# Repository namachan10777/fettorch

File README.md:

# fettorch
bootstrap式モータードライバ

# TODO
 * 回路定数の決定
 * 電源供給基板の設計
# Licence
MIT Licence

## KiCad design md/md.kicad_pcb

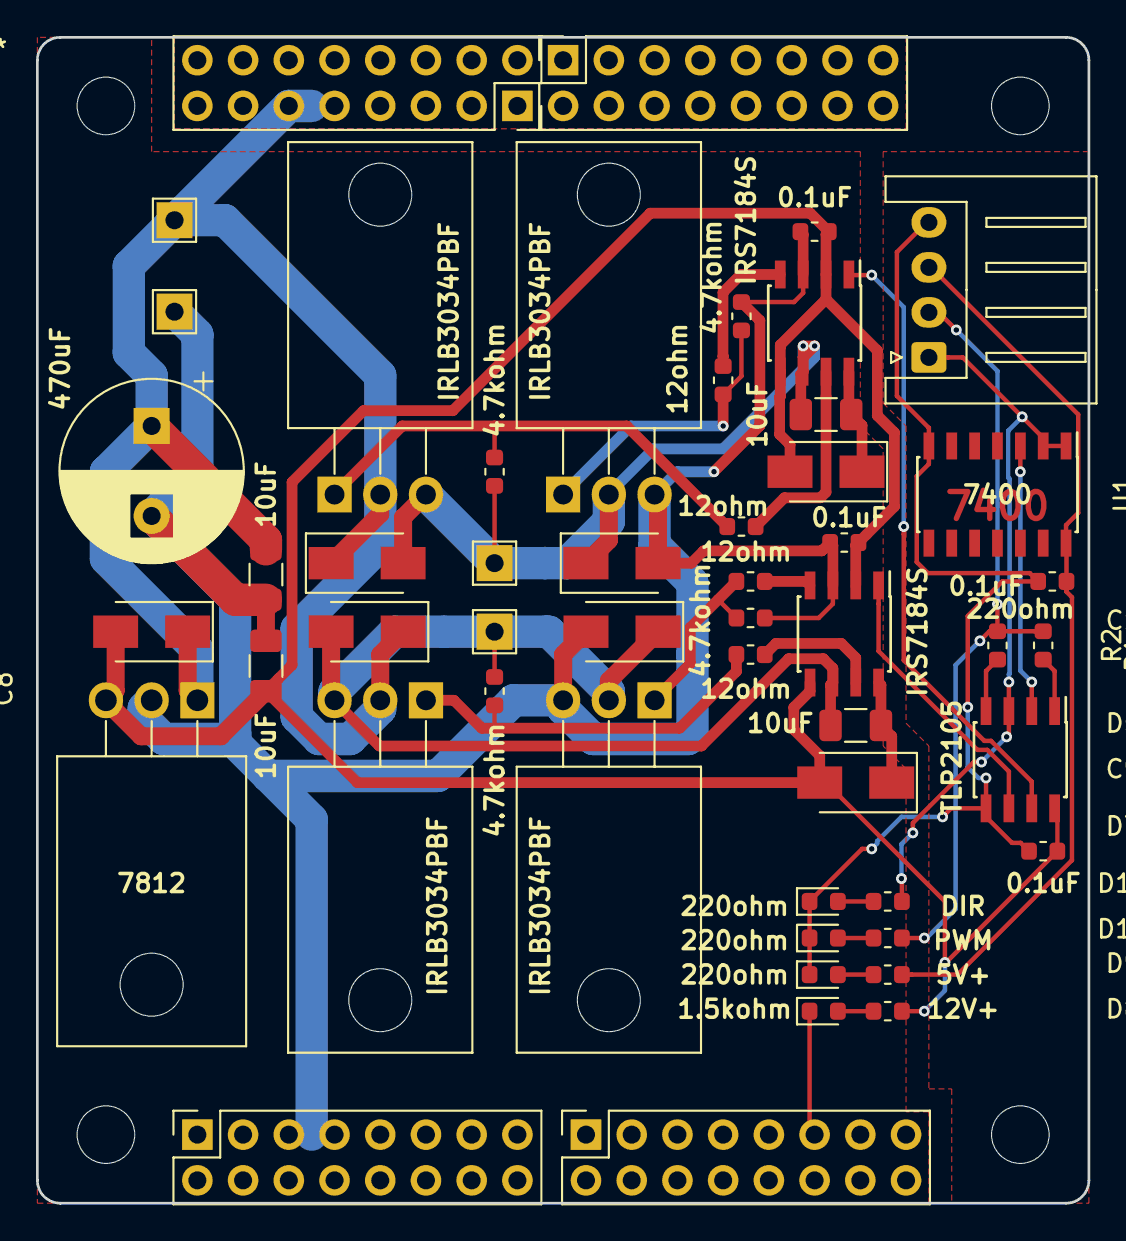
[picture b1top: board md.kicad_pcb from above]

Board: 2 copper layers, 58.4 x 64.8 mm, 52 parts (0 on the bottom side), 28 nets.

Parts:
C1, C2, C3, C10: 0.1uF; C_0603_1608Metric
C4, C5, C8, C9: 10uF; C_1206_3216Metric
C7: 470uF; CP_Radial_D10.0mm_P5.00mm
D1, D2, D3, D4, D5, D6, D7: S1AFSDKR-ND; D_SMA
D8: SMLE13BC8TT86; LED_0603_1608Metric
D9: OSOR1608C1A; LED_0603_1608Metric
D10, D11: SML-E12M8WT86; LED_0603_1608Metric
J1: Interface; JST_XH_S04B-XH-A_1x04_P2.50mm_Horizontal
J2: PowerInput+; TestPoint_THTPad_2.0x2.0mm_Drill1.0mm
J3: PowerInput-; TestPoint_THTPad_2.0x2.0mm_Drill1.0mm
J4: OUT+; TestPoint_THTPad_2.0x2.0mm_Drill1.0mm
J5: OUT-; TestPoint_THTPad_2.0x2.0mm_Drill1.0mm
J6, J7: PowerInput+; PinSocket_2x08_P2.54mm_Vertical
J8, J9: PowerInput-; PinSocket_2x08_P2.54mm_Vertical
Q1, Q3: IRLB3034PBF; TO-220-3_Horizontal_TabDown
Q2, Q4: IR3034PBF; TO-220-3_Horizontal_TabDown
R1, R2, R12, R13, R14: 220ohm; R_0603_1608Metric
R3, R4, R9, R10: 12ohm; R_0603_1608Metric
R5, R6, R7, R8: 4.7kohm; R_0603_1608Metric
R11: 1.5kohm; R_0603_1608Metric
U1: SN74HC00; SOIC-14_3.9x8.7mm_P1.27mm
U3: TLP2105; SOIC-8_3.9x4.9mm_P1.27mm
U4, U6: IR7184S; SOIC-8_3.9x4.9mm_P1.27mm
U5: LM7812; TO-220F-3_Horizontal_TabDown

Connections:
+5V: C1.1, J1.3, R12.1, U1.14
+12V: C2.2, C3.1, C8.1, C10.1, D1.2, D4.2, D7.2, R11.1, U3.8, U4.2, U4.5, U5.3, U6.2, U6.5
+24V: C5.1, C7.1, D2.1, D4.1, D5.1, J2.1, J6.1, J6.2, J6.3, J6.4, J6.5, J6.6, J6.7, J6.8, J6.9, J6.10, J6.11, J6.12, J6.13, J6.14, J6.15, J6.16, J7.1, J7.2, J7.3, J7.4, J7.5, J7.6, J7.7, J7.8, J7.9, J7.10, J7.11, J7.12, J7.13, J7.14, J7.15, J7.16, Q1.2, Q3.2, U5.1
/DIR: J1.1, R13.1, U1.1, U1.2, U3.3
/OUTA: U3.7, U4.1
/OUTB: U3.6, U6.1
/PWM: J1.2, R1.1, R2.1, R14.1
GND: C1.2, C2.1, D9.1, D10.1, D11.1, J1.4, U1.7, U3.5
GNDPWR: C3.2, C5.2, C7.2, C8.2, C10.2, D3.2, D6.2, D8.1, J3.1, J8.1, J8.2, J8.3, J8.4, J8.5, J8.6, J8.7, J8.8, J8.9, J8.10, J8.11, J8.12, J8.13, J8.14, J8.15, J8.16, J9.1, J9.2, J9.3, J9.4, J9.5, J9.6, J9.7, J9.8, J9.9, J9.10, J9.11, J9.12, J9.13, J9.14, J9.15, J9.16, Q2.3, Q4.3, R6.2, R8.2, U4.3, U5.2, U6.3
unnamed: C4.1, D1.1, U4.8
unnamed: C4.2, D2.2, D3.1, J4.1, Q1.3, Q2.2, R5.2, U4.6
unnamed: C9.1, D7.1, U6.8
unnamed: C9.2, D5.2, D6.1, J5.1, Q3.3, Q4.2, R7.2, U6.6
unnamed: D8.2, R11.2
unnamed: D9.2, R12.2
unnamed: D10.2, R13.2
unnamed: D11.2, R14.2
unnamed: Q1.1, R3.1, R5.1
unnamed: Q2.1, R4.1, R6.1
unnamed: Q3.1, R7.1, R9.1
unnamed: Q4.1, R8.1, R10.1
unnamed: R1.2, U3.1
unnamed: R2.2, U3.4
unnamed: R3.2, U4.7
unnamed: R4.2, U4.4
unnamed: R9.2, U6.7
unnamed: R10.2, U6.4
unnamed: U1.3, U3.2

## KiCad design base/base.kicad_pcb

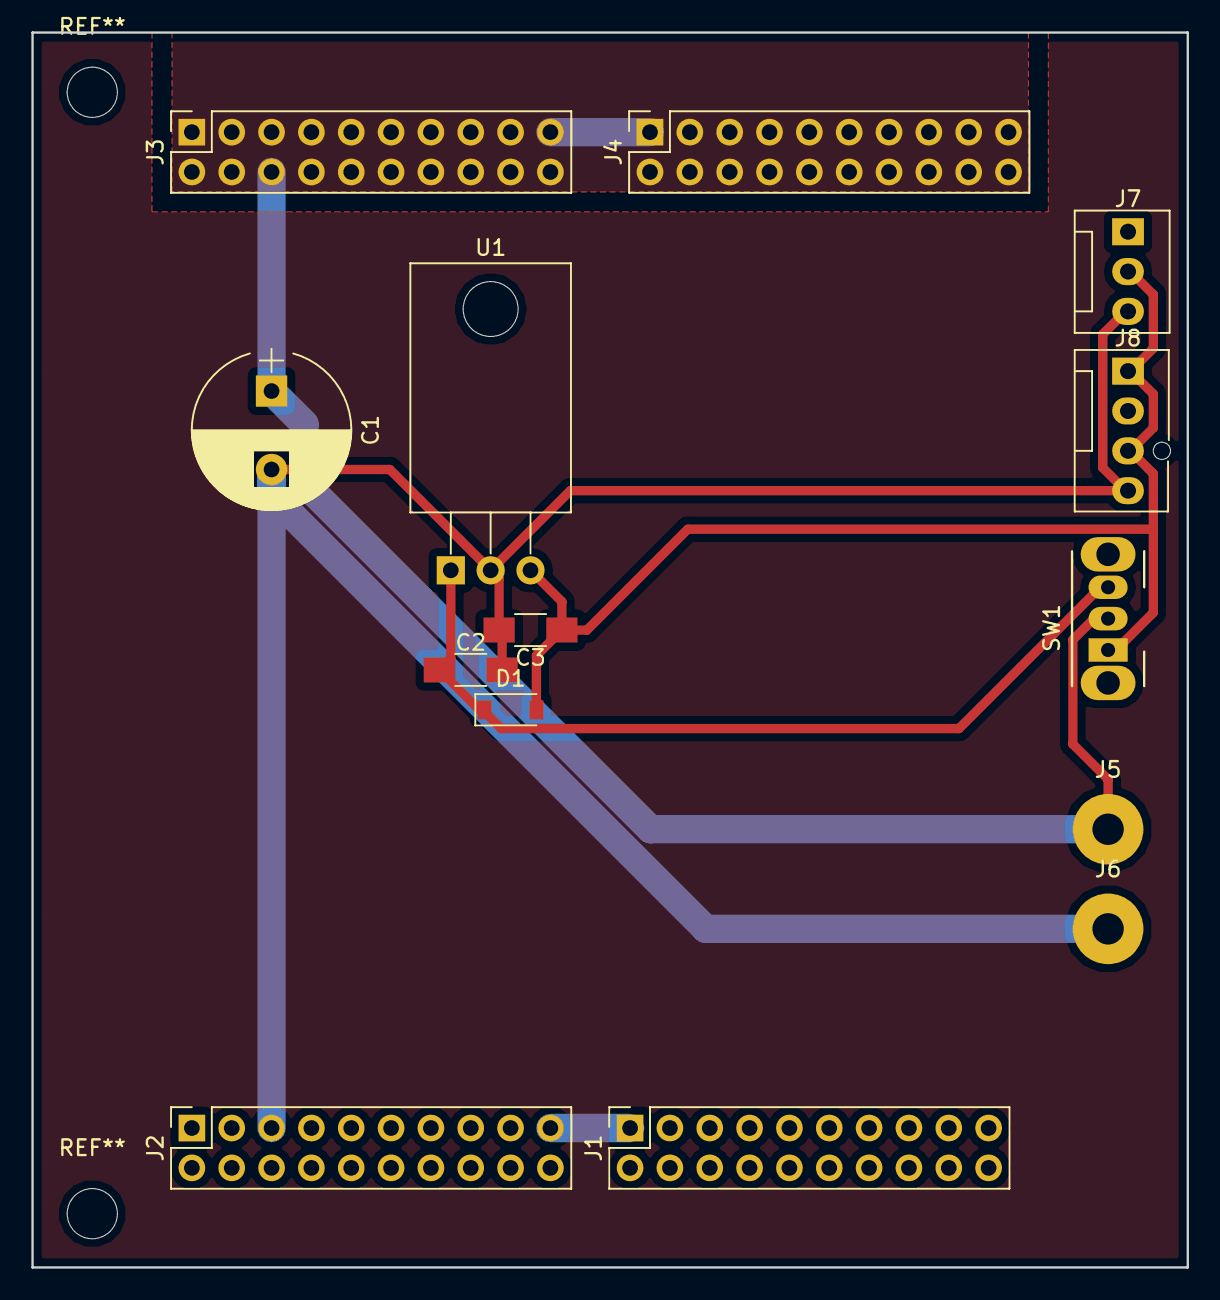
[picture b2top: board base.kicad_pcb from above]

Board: 2 copper layers, 73.7 x 78.7 mm, 14 parts (0 on the bottom side), 4 nets.

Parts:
C1: CP; CP_Radial_D10.0mm_P5.00mm
C2, C3: 10uF; C_1206_HandSoldering
D1: D; D_SOD-123
J1, J2: POWER_OUTPUT-; Socket_Strip_Straight_2x10_Pitch2.54mm
J3, J4: POWER_OUTPUT+; Socket_Strip_Straight_2x10_Pitch2.54mm
J5: POWER_INPUT+; SolderWirePad_single_2mmDrill
J6: POWER_INPUT-; SolderWirePad_single_2mmDrill
J7: FAN_3pin; Fan_Pin_Header_Straight_1x03
J8: FAN_4pin; Fan_Pin_Header_Straight_1x04
SW1: VSELECT; SW_CuK_OS102011MA1QN1_SPDT_Angled
U1: LM7812_TO220; TO-220-3_Horizontal

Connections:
+12V: C3.1, D1.2, J7.2, J8.1, J8.3, SW1.1, U1.3
+24V: C1.1, J3.1, J3.2, J3.3, J3.4, J3.5, J3.6, J3.7, J3.8, J3.9, J3.10, J3.11, J3.12, J3.13, J3.14, J3.15, J3.16, J3.17, J3.18, J3.19, J3.20, J4.1, J4.2, J4.3, J4.4, J4.5, J4.6, J4.7, J4.8, J4.9, J4.10, J4.11, J4.12, J4.13, J4.14, J4.15, J4.16, J4.17, J4.18, J4.19, J4.20, J5.1, SW1.2
GNDPWR: C1.2, C2.2, C3.2, J1.1, J1.2, J1.3, J1.4, J1.5, J1.6, J1.7, J1.8, J1.9, J1.10, J1.11, J1.12, J1.13, J1.14, J1.15, J1.16, J1.17, J1.18, J1.19, J1.20, J2.1, J2.2, J2.3, J2.4, J2.5, J2.6, J2.7, J2.8, J2.9, J2.10, J2.11, J2.12, J2.13, J2.14, J2.15, J2.16, J2.17, J2.18, J2.19, J2.20, J6.1, J7.3, J8.4, U1.2
unnamed: C2.1, D1.1, SW1.3, U1.1

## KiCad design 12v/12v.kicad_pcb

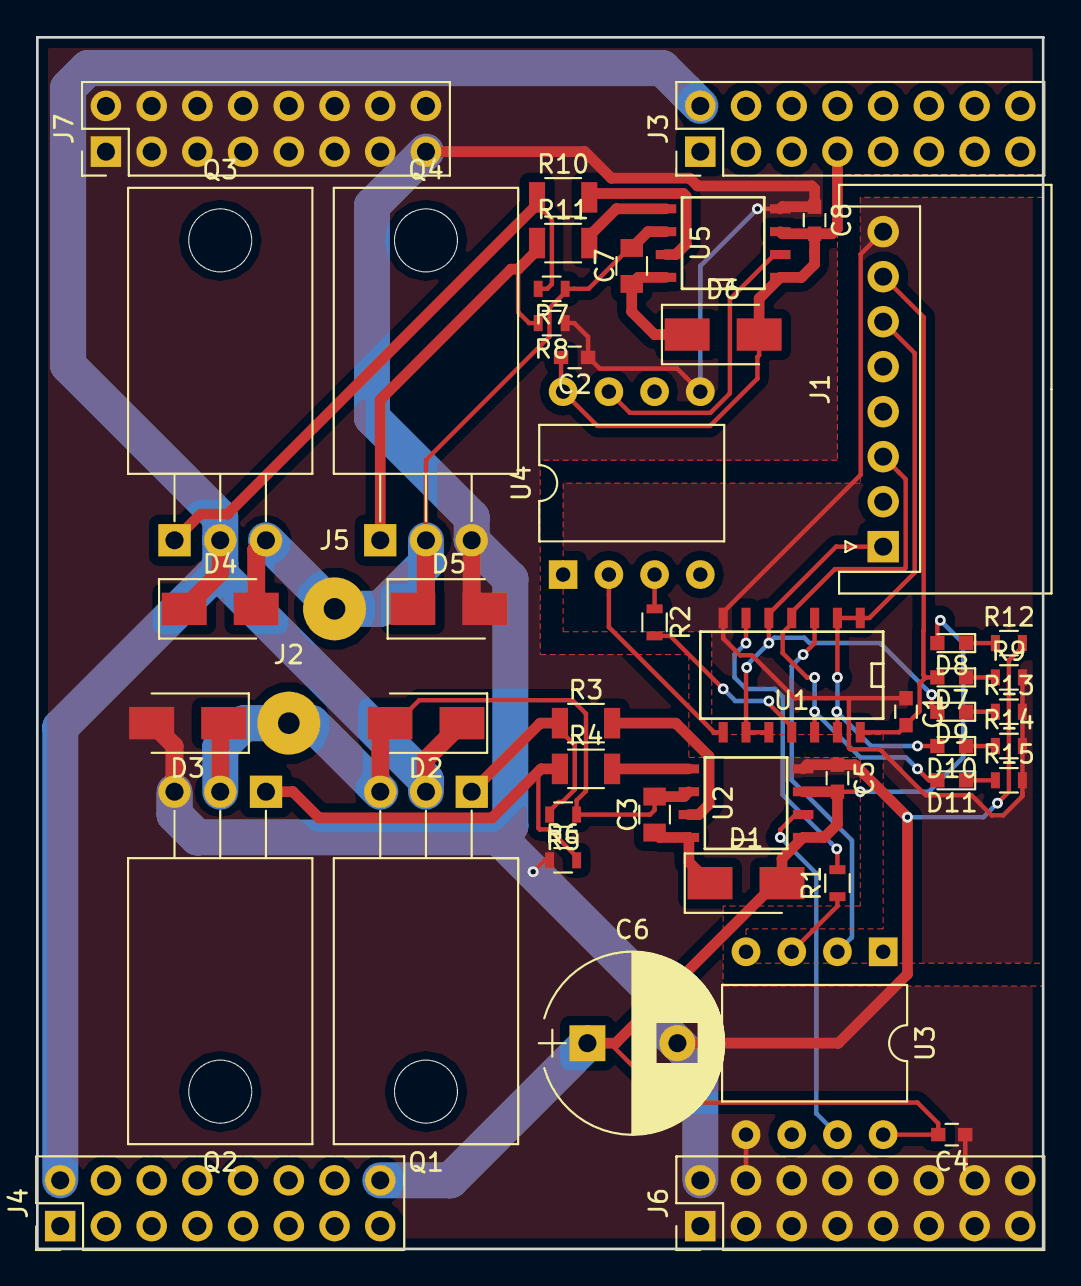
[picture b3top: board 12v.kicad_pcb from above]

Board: 2 copper layers, 55.9 x 67.3 mm, 50 parts (0 on the bottom side), 32 nets.

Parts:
C1, C2, C4, C5, C8: passC; C_0603
C3, C7: bootC; C_0805
C6: PowerCP; CP_Radial_D10.0mm_P5.00mm
D1, D6: bootD; D_SMA
D2, D3, D4, D5: RevD; D_SMA
D7, D8, D9, D10, D11: LED; LED_0603
J1: Conn_01x08_Female; JST_XH_S08B-XH-A_08x2.50mm_Angled
J2, J5: Conn_01x01; SolderWirePad_single_1-2mmDrill
J3, J4, J6, J7: Conn_02x08_Counter_Clockwise; Pin_Header_Straight_2x08_Pitch2.54mm
Q1: FET_A_UP; TO-220-3_Horizontal
Q2: FET_A_DOWN; TO-220-3_Horizontal
Q3: FET_B_UP; TO-220-3_Horizontal
Q4: FET_B_DOWN; TO-220-3_Horizontal
R1, R2: tlp-in-R; R_0603
R3, R4, R10, R11: GateR; R_1206
R5, R6, R7, R8: PullR; R_0603
R9: LEDR; R_0603
R12, R13, R14, R15: R; R_0603
U1: 7400; SOIC-14_N
U2, U5: IRS2302; SOIC-8-N
U3, U4: TLP2955; DIP-8_W10.16mm

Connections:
+5V: C1.2, D7.2, J1.7, U1.14
+12V: C2.2, C4.2, C5.2, C6.1, C8.2, D1.2, D2.1, D4.1, D6.2, D8.2, J3.1, J3.2, J3.3, J3.4, J3.5, J3.6, J3.7, J3.8, J3.9, J3.10, J3.11, J3.12, J3.13, J3.14, J3.15, J3.16, J4.1, J4.2, J4.3, J4.4, J4.5, J4.6, J4.7, J4.8, J4.9, J4.10, J4.11, J4.12, J4.13, J4.14, J4.15, J4.16, Q1.2, Q3.2, U2.1, U2.3, U3.8, U4.8, U5.1, U5.3
GND: C1.1, J1.8, R9.2, R13.2, R14.2, R15.2, U1.7
GNDPWR: C2.1, C4.1, C5.1, C6.2, C8.1, D3.2, D5.2, J6.1, J6.2, J6.3, J6.4, J6.5, J6.6, J6.7, J6.8, J6.9, J6.10, J6.11, J6.12, J6.13, J6.14, J6.15, J6.16, J7.1, J7.2, J7.3, J7.4, J7.5, J7.6, J7.7, J7.8, J7.9, J7.10, J7.11, J7.12, J7.13, J7.14, J7.15, J7.16, Q2.3, Q4.3, R6.1, R8.1, R12.2, U2.4, U3.5, U4.5, U5.4
INA: D9.2, J1.1, U1.5, U1.9, U1.10
INB: D10.2, J1.6, U1.1, U1.2, U1.13
unnamed: C3.1, D1.1, U2.8
unnamed: C3.2, D2.2, D3.1, J2.1, Q1.3, Q2.2, R5.1, U2.6
unnamed: C7.1, D6.1, U5.8
unnamed: C7.2, D4.2, D5.1, J5.1, Q3.3, Q4.2, R7.1, U5.6
unnamed: D7.1, R9.1
unnamed: D8.1, R12.1
unnamed: D9.1, R13.1
unnamed: D10.1, R14.1
unnamed: D11.1, R15.1
unnamed: Q1.1, R3.1, R5.2
unnamed: Q2.1, R4.1, R6.2
unnamed: Q3.1, R7.2, R10.1
unnamed: Q4.1, R8.2, R11.1
unnamed: R1.1, U3.3
unnamed: R1.2, U1.6
unnamed: R2.1, U4.3
unnamed: R2.2, U1.11
unnamed: R3.2, U2.7
unnamed: R4.2, U2.5
unnamed: R10.2, U5.7
unnamed: R11.2, U5.5
unnamed: U1.3, U3.2
unnamed: U1.8, U4.2
OUTA: U2.2, U3.7
OUTB: U4.7, U5.2
PWM: D11.2, J1.3, U1.4, U1.12

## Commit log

2018-01-20 add submodule udon-kilib
2018-01-20 add empty project 12v
2018-01-20 update udon-kilib 'add irs2108' IRS2108を追加したので追従
2018-01-20 setting udon-kilib
2018-01-20 update udon-kilib
2018-01-20 draw main circuit
2018-01-21 complete drawing circuit diagram
    暫定的に全てスルーホールで部品を割付
2018-01-22 improve circuit LEDの追加、コネクタの互換性
2018-01-22 change FET package TO-220 -> TO-251
2018-01-22 place packages
2018-01-23 conn_02x10 -> 02x08 * 2
2018-01-23 draw gerber data
2018-01-23 add project file
2018-01-23 add schematic
2018-01-26 add pcb file
2018-01-27 revision README
2018-03-06 use SMD parts
2018-03-06 fix parts 抵抗が全部LEDになっていた
2018-03-25 use SMD parts.(Not Wired)
2018-03-25 wiring
2018-03-25 fix solid gnd area
2018-03-25 design 24v ver
2018-03-25 fix resist mask area
2018-03-25 fix outline
2018-03-25 setting 3d view
2018-04-29 integrate 12v and 24v
2018-04-29 add img
2018-05-24 add note
2018-05-24 TLP2105を使うようschを変更
2018-05-24 fix note
2018-06-17 バグでは?
2018-06-17 アドホック太郎
2018-06-18 use TLP2105
2018-06-30 fix typo
2018-07-15 delete submodule udon-kilib
    submodule面倒
2018-07-15 add IRS7184 and TLP2105 to lib
2018-07-15 fix schematic
2018-07-15 swap Inteface direction
2018-07-15 supply passcon
2018-07-15 だいたい配置出来た
2018-07-15 drew pcb pattern
2018-07-15 finished working
2018-07-17 upgrade kicad
2018-07-23 add gerber file rename script
2018-09-15 update KiCAD 5.x (schematic)
2018-09-15 add sockets
2018-09-15 add LEDs
2018-09-15 fix LEDs size
2018-09-15 fix diode placement
2018-09-15 update pcb
2018-09-15 add mask
2018-09-16 add current limit regisiter for TLP2105
2018-09-18 fix capacitor arrangement
2018-09-21 improve line design
2018-09-30 complete md
2018-09-30 add base
2018-10-07 PCBのガーバー出力
2018-10-07 ignore gerber
2018-10-07 change regul
2018-11-18 rewrite sch
2018-11-23 assign packages
2018-12-06 パターン作った
2018-12-07 VSと電位の基準繋げてなかった
2018-12-07 半田盛り盛り森鴎外
2018-12-07 ベタGNDは綺麗に
2018-12-07 add silks
